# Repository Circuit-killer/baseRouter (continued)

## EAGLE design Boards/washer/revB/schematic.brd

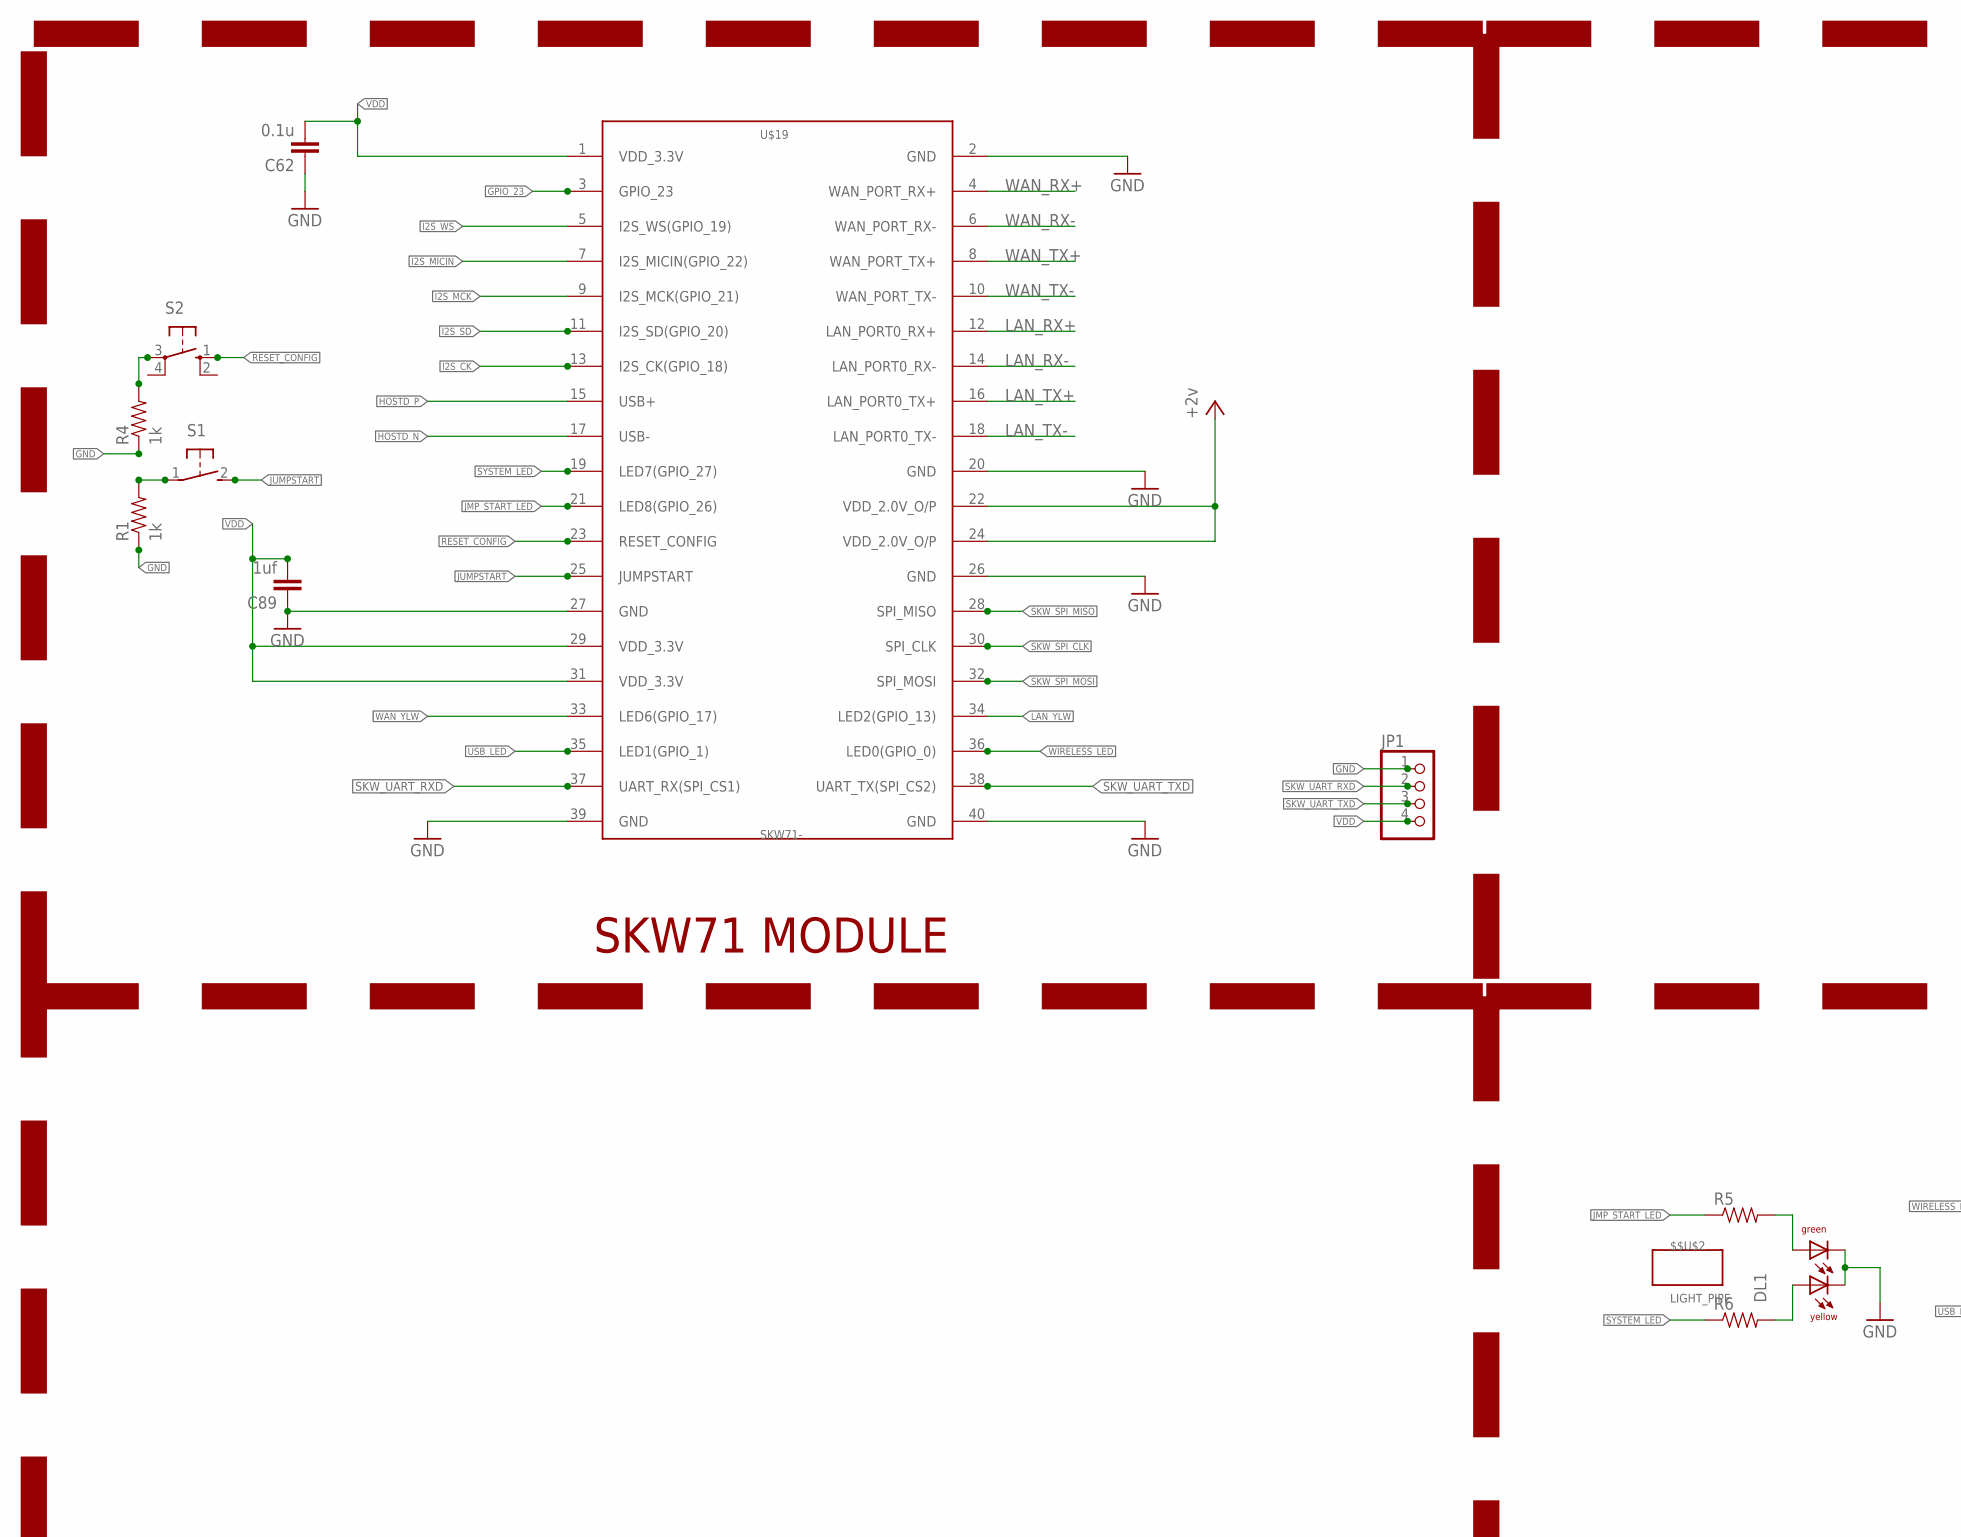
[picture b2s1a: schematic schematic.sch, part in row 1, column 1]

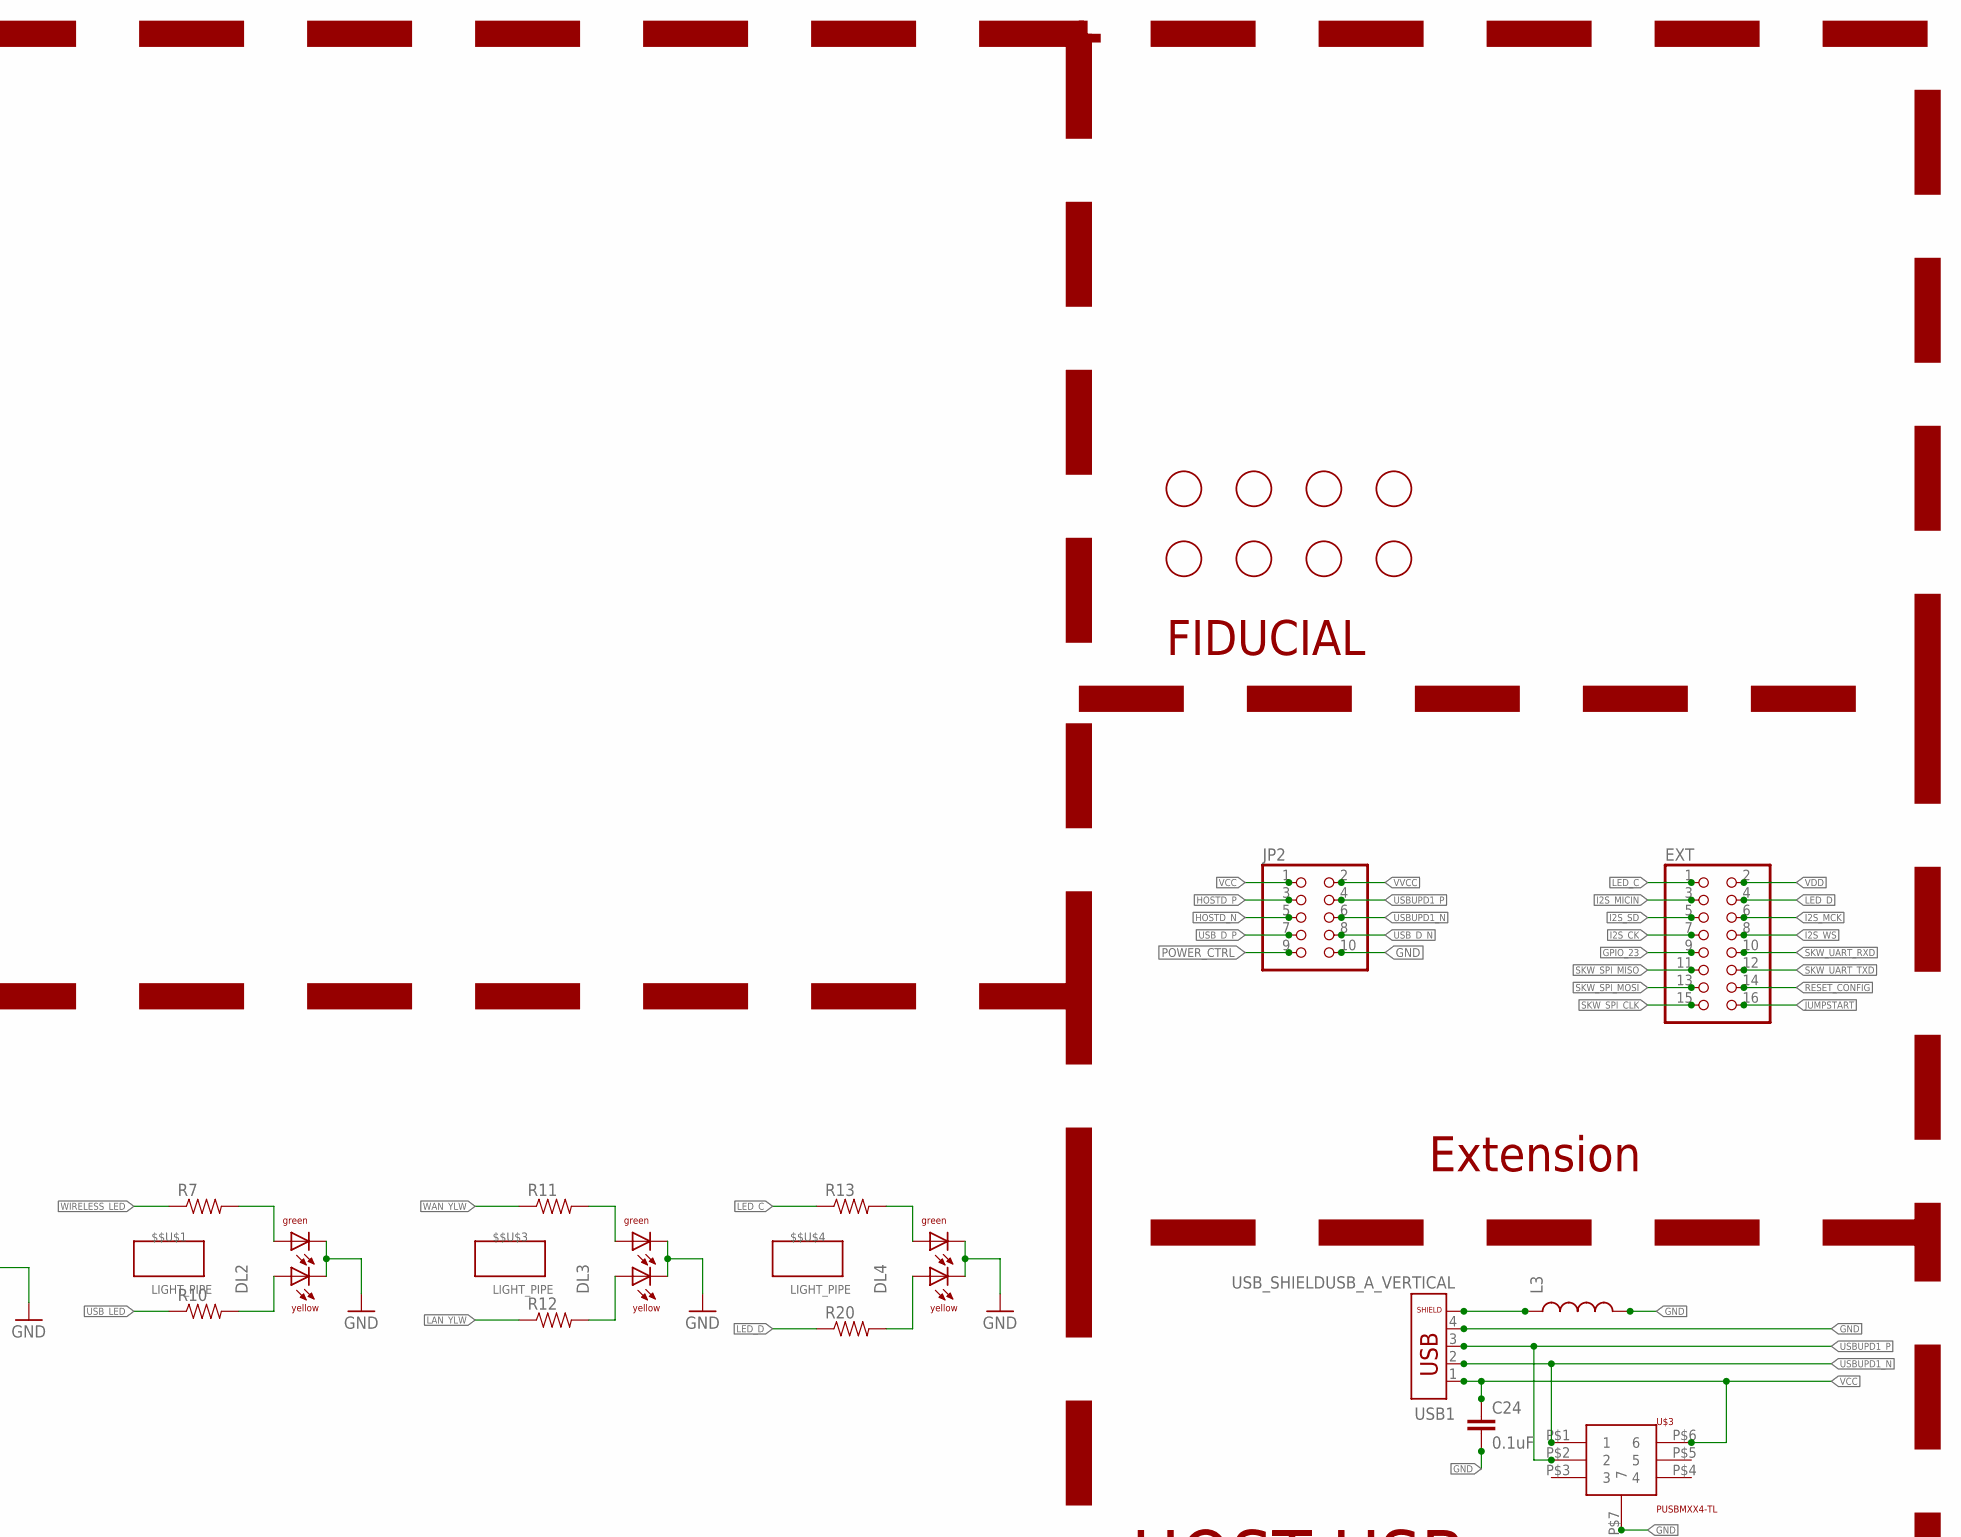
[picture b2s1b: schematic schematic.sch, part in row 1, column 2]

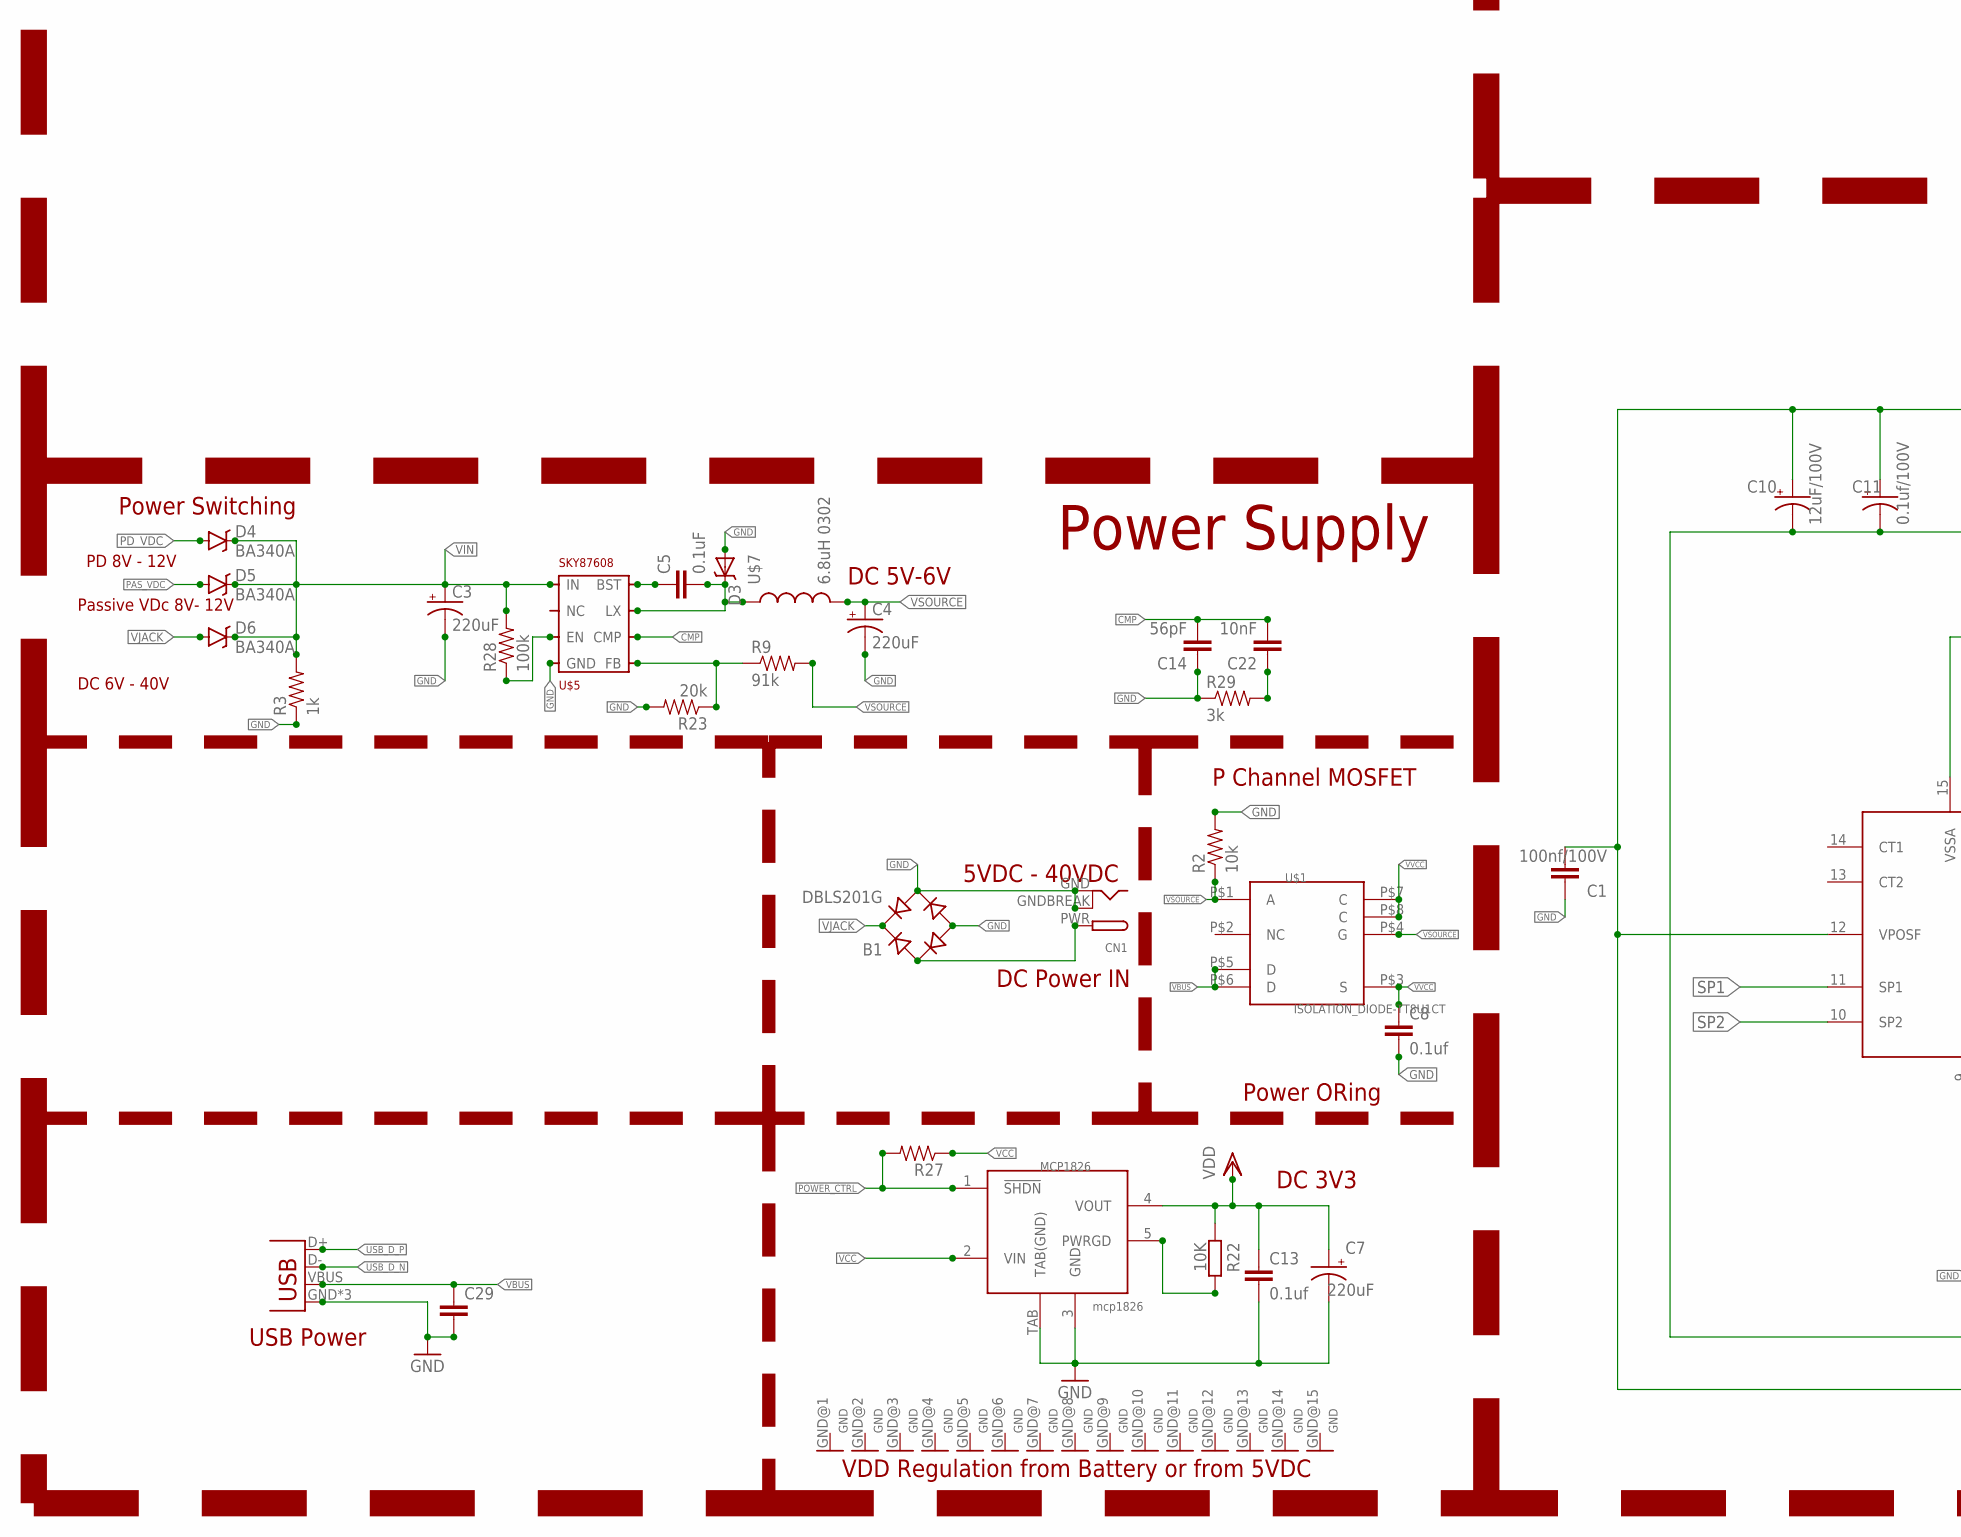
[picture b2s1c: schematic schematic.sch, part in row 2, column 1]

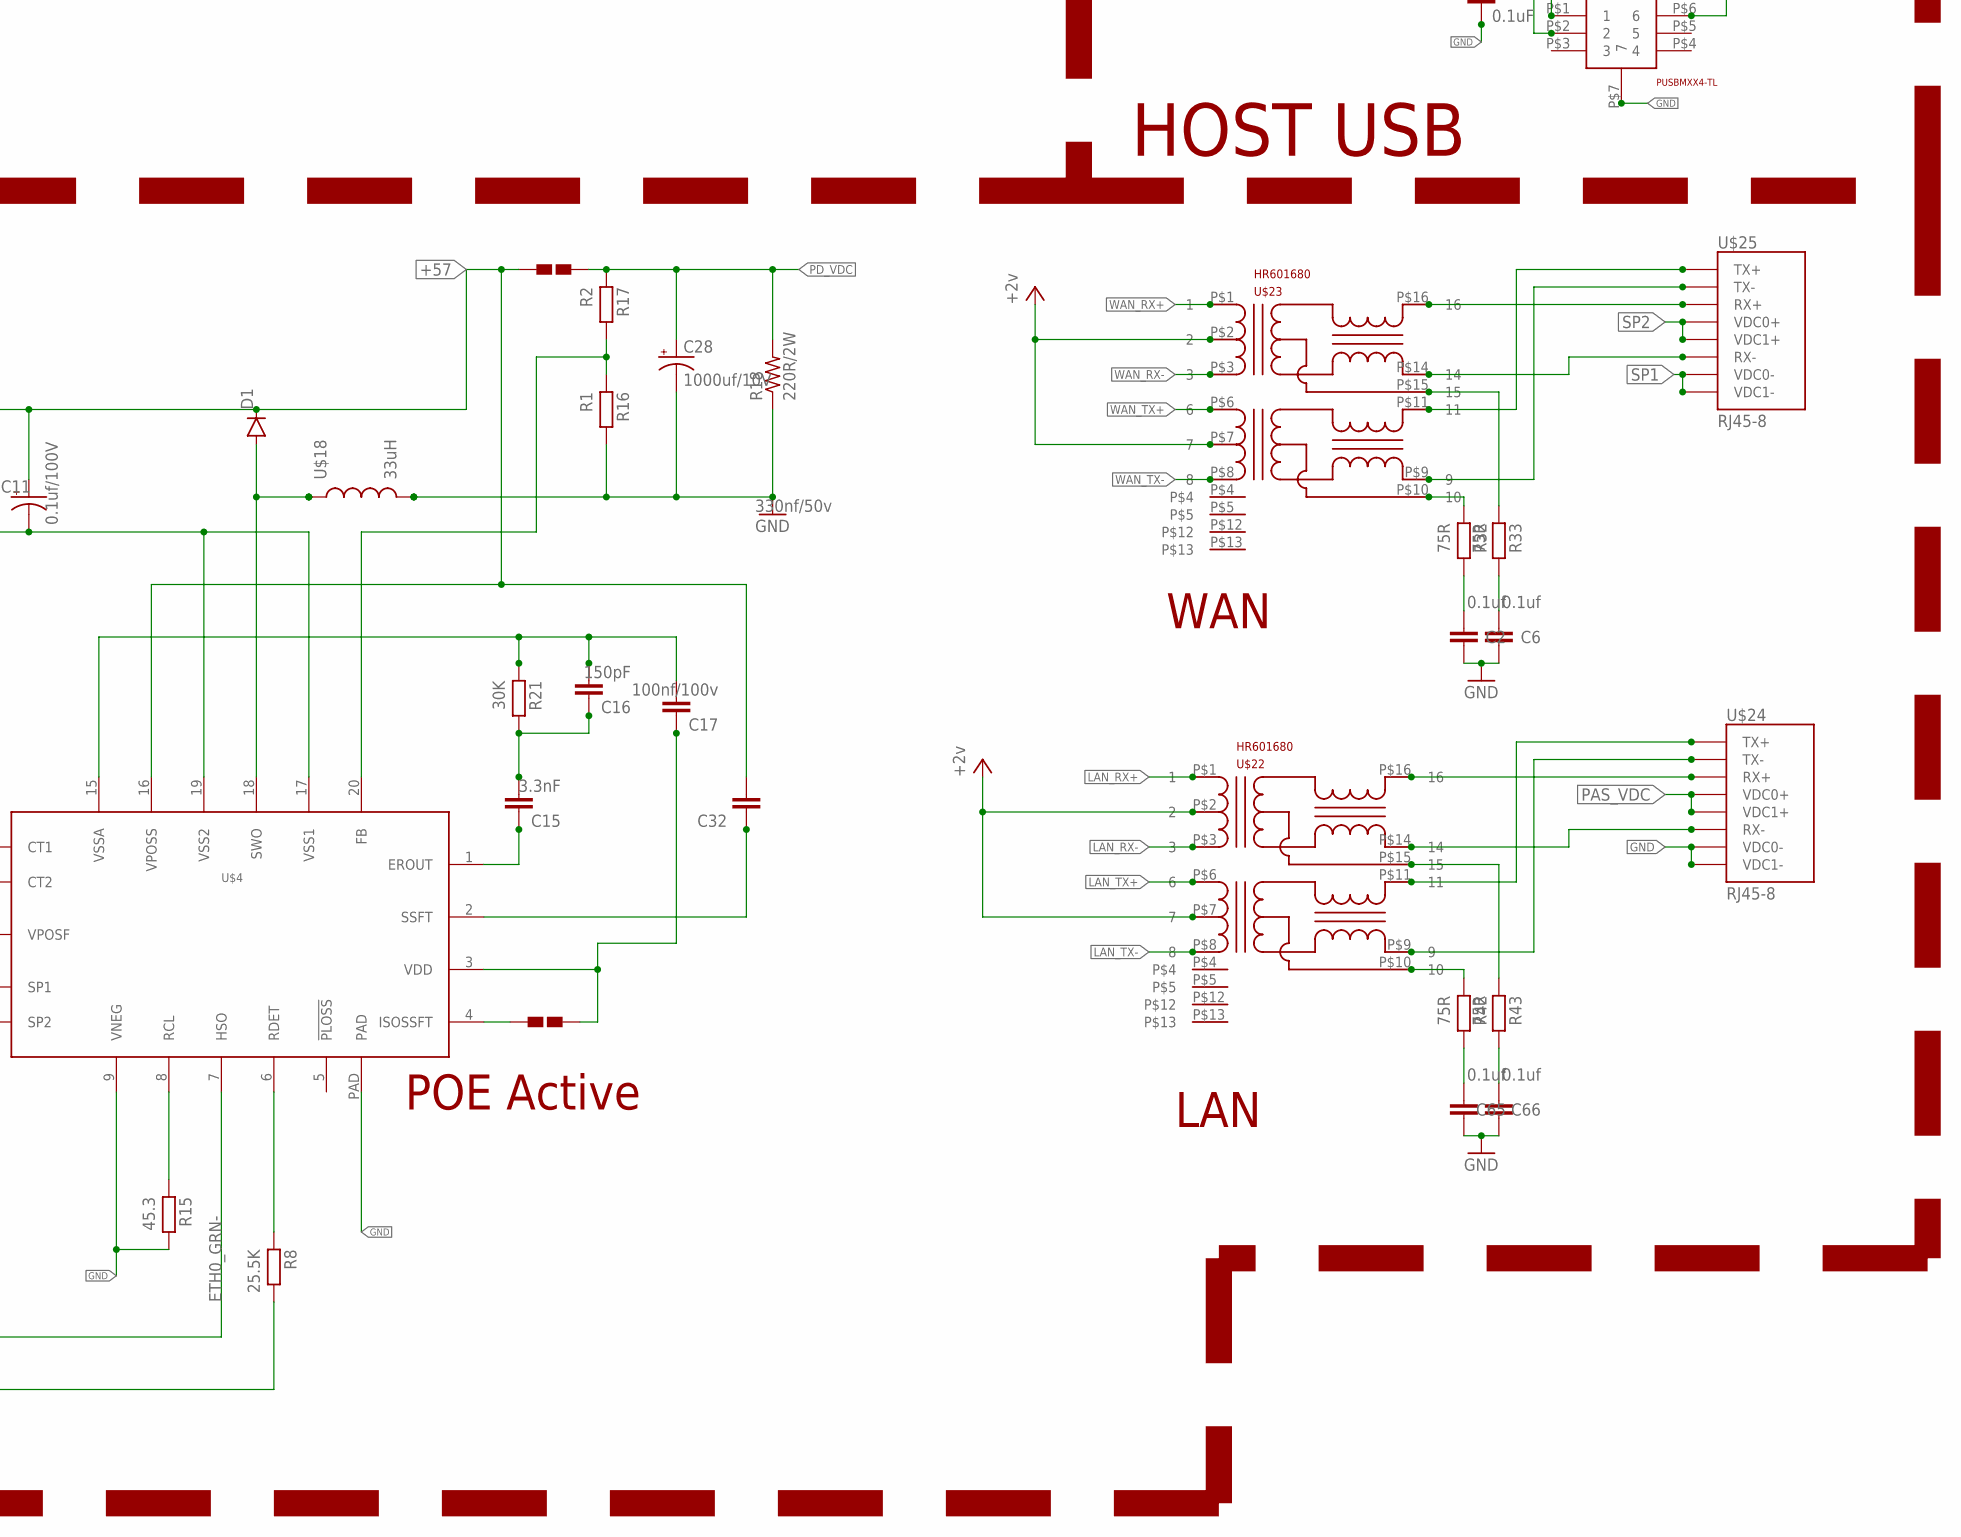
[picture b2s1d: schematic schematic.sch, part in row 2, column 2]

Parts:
$$U$1, $$U$2, $$U$3, $$U$4: LIGHT_PIPE; LIGHT-PIPE
B1: DBLS201G; DBS
C1: 100nf/100V; C0805
C2, C6, C65, C66: 0.1uf; C0603
C3: 220uF; E3,5-10
C4, C7: 220uF; E5-10,5
C5, C24: 0.1uF; 0402-CAP
C8, C13: 0.1uf; C0402
C10: 12uF/100V; E2,5-6E
C11: 0.1uf/100V; E2-5
C14: 56pF; 0402-CAP
C15: 3.3nF; C0805
C16: 150pF; C0805
C17: 100nf/100v; C0805
C22: 10nF; 0402-CAP
C28: 1000uf/10V; E5-13
C29: CAP0402-CAP; 0402-CAP
C32: 330nf/50v; C0805
C62: 0.1u; C0603
C89: 1uf; C0603
CN1: DCBARRELPTH; DCJACK_2MM_PTH
D1: DIODESMC/DO-214AB; SMC
D3: DIODE-SCHOTTKY_; SMA-DIODE
D4, D5, D6: BA340A; SMA-DIODE
DL1, DL2, DL3, DL4: DUOLED-1X2; DUOLED-C-0603
EXT: PINHD-2X8; 2X08
JP1: PINHD-1X4; 1X04
JP2: PINHD-2X5; 2X05
JP4: USB-MICROB
L3: INDUCTOR0402; C0402
MCP1826: mcp1826; SOT223-5
R1, R3, R4: 1k; 0402-RES
R2: 10k; 0402-RES
R5, R6, R7, R10, R11, R12, R13, R20, R27: RESISTOR0402-RES; 0402-RES
R8: 25.5K; R0603
R9: 91k; 0402-RES
R15: 45.3; R0603
R16: R1; R0603
R17: R2; R0603
R18: 220R/2W; R2512
R21: 30K; R0603
R22: 10K; R0402
R23: 20k; 0402-RES
R28: 100k; 0402-RES
R29: 3k; 0402-RES
R32, R33, R42, R43: 75R; R0603
S1: 31-XX; B3F-31XX
S2: 10-XX; B3F-10XX
U$1: ISOLATION_DIODE-TT8U1CT; 8-TSST
U$3: PUSBMXX4-TL
U$4: SI3402
U$5: SKY87608; 8PIN-SOP-8L-EP
U$7: 6.8uH 0302; SRN6045
U$9, U$11, U$12, U$13, U$14, U$15, U$16, U$17: FIDUCIAL; FIDUCIAL_1MM
U$10, U$28: SOL-PAD-OPEN
U$18: 33uH; INDUCTOR-10X9.8X6
U$19: SKW71-; SKW71-SMT
U$22, U$23: HR601680; SOIC-16
U$24, U$25: RJ45-8; RJHSE-5080-ND
USB1: USB_SHIELDUSB_A_VERTICAL; USB_A_VERTICAL_PTH

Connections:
+2V: U$19.22 (VDD_2.0V_O/P), U$19.24 (VDD_2.0V_O/P), U$22.P$2 (2), U$22.P$7 (7), U$23.P$2 (2), U$23.P$7 (7)
+57: C1.2, C10.+, C11.+, C32.2, D1.C, R8.2, U$4.12 (VPOSF), U$4.16 (VPOSS), U$28.P$1 (1)
CMP: C14.2, C22.2, U$5.P$6 (CMP)
ETH0_GRN-: C10.-, C11.-, U$4.7 (HSO), U$4.17 (VSS1), U$4.19 (VSS2)
GND: B1.-, B1.AC2, C1.1, C2.1, C3.-, C4.-, C6.1, C7.-, C8.2, C13.2, C14.1, C24.2, C28.-, C29.2, C62.1, C65.1, C66.1, C89.1, CN1.GND, CN1.GNDBREAK, D3.A, DL1.C1, DL1.C2, DL2.C1, DL2.C2, DL3.C1, DL3.C2, DL4.C1, DL4.C2, JP1.1, JP2.10, JP4.GND, JP4.MT1 (GND), JP4.MT2 (GND), L3.2, MCP1826.3 (GND), MCP1826.GND@1 (GND), MCP1826.GND@2 (GND), MCP1826.GND@3 (GND), MCP1826.GND@4 (GND), MCP1826.GND@5 (GND), MCP1826.GND@6 (GND), MCP1826.GND@7 (GND), MCP1826.GND@8 (GND), MCP1826.GND@9 (GND), MCP1826.GND@10 (GND), MCP1826.GND@11 (GND), MCP1826.GND@12 (GND), MCP1826.GND@13 (GND), MCP1826.GND@14 (GND), MCP1826.GND@15 (GND), MCP1826.TAB (TAB(GND)), R1.1, R2.2, R3.1, R4.1, R15.2, R16.2, R18.1, R23.2, R29.1, U$3.P$7 (7), U$4.9 (VNEG), U$4.PAD, U$5.P$4 (GND), U$18.P$2 (2), U$19.2 (GND), U$19.20 (GND), U$19.26 (GND), U$19.27 (GND), U$19.39 (GND), U$19.40 (GND), U$24.P$7 (VDC0-), U$24.P$8 (VDC1-), USB1.4
GPIO_23: EXT.9, U$19.3 (GPIO_23)
HOSTD_N: JP2.5, U$19.17 (USB-)
HOSTD_P: JP2.3, U$19.15 (USB+)
I2S_CK: EXT.7, U$19.13 (I2S_CK(GPIO_18))
I2S_MCK: EXT.6, U$19.9 (I2S_MCK(GPIO_21))
I2S_MICIN: EXT.3, U$19.7 (I2S_MICIN(GPIO_22))
I2S_SD: EXT.5, U$19.11 (I2S_SD(GPIO_20))
I2S_WS: EXT.8, U$19.5 (I2S_WS(GPIO_19))
JMP_START_LED: R5.1, U$19.21 (LED8(GPIO_26))
JUMPSTART: EXT.16, S1.2 (S), U$19.25 (JUMPSTART)
LAN_RX+: U$19.12 (LAN_PORT0_RX+), U$22.P$1 (1)
LAN_RX-: U$19.14 (LAN_PORT0_RX-), U$22.P$3 (3)
LAN_TX+: U$19.16 (LAN_PORT0_TX+), U$22.P$6 (6)
LAN_TX-: U$19.18 (LAN_PORT0_TX-), U$22.P$8 (8)
LAN_YLW: R12.1, U$19.34 (LED2(GPIO_13))
LED_C: EXT.1, R13.1
LED_D: EXT.4, R20.1
unnamed: DL2.A1, R7.2
unnamed: C5.2, D3.C, U$5.P$2 (LX), U$7.1
unnamed: DL1.A1, R5.2
unnamed: DL2.A2, R10.2
unnamed: R1.2, S1.1
unnamed: C16.2, C17.2, R21.1, U$4.15 (VSSA)
unnamed: C15.2, C16.1, R21.2
unnamed: R8.1, U$4.6 (RDET)
unnamed: R15.1, U$4.8 (RCL)
unnamed: R4.2, S2.3
unnamed: U$4.4 (ISOSSFT), U$10.P$1 (1)
unnamed: C17.1, U$4.3 (VDD), U$10.P$2 (2)
unnamed: C15.1, U$4.1 (EROUT)
unnamed: C32.1, U$4.2 (SSFT)
unnamed: R16.1, R17.2, U$4.20 (FB)
unnamed: DL3.A2, R12.2
unnamed: DL4.A1, R13.2
unnamed: MCP1826.5 (PWRGD), R22.2
unnamed: R28.1, U$5.P$7 (EN)
unnamed: C5.1, U$5.P$8 (BST)
unnamed: R9.1, R23.1, U$5.P$5 (FB)
unnamed: DL4.A2, R20.2
unnamed: DL3.A1, R11.2
unnamed: C22.1, R29.2
unnamed: D1.A, U$4.18 (SWO), U$18.P$1 (1)
unnamed: DL1.A2, R6.2
unnamed: L3.1, USB1.P$3 (5)
unnamed: C2.2, R32.2
unnamed: B1.AC1, CN1.PWR
unnamed: C6.2, R33.2
unnamed: U$23.P$16 (16), U$25.P$3 (RX+)
unnamed: U$23.P$14 (14), U$25.P$6 (RX-)
unnamed: R33.1, U$23.P$15 (15)
unnamed: U$23.P$11 (11), U$25.P$1 (TX+)
unnamed: U$23.P$9 (9), U$25.P$2 (TX-)
unnamed: R32.1, U$23.P$10 (10)
unnamed: R42.1, U$22.P$10 (10)
unnamed: U$22.P$9 (9), U$24.P$2 (TX-)
unnamed: U$22.P$11 (11), U$24.P$1 (TX+)
unnamed: R43.1, U$22.P$15 (15)
unnamed: U$22.P$14 (14), U$24.P$6 (RX-)
unnamed: U$22.P$16 (16), U$24.P$3 (RX+)
unnamed: C65.2, R42.2
unnamed: C66.2, R43.2
PAS_VDC: D5.A, U$24.P$4 (VDC0+), U$24.P$5 (VDC1+)
PD_VDC: C28.+, D4.A, R17.1, R18.2, U$28.P$2 (2)
POWER_CTRL: JP2.9, MCP1826.1 (!SHDN), R27.2
RESET_CONFIG: EXT.14, S2.1 (S), U$19.23 (RESET_CONFIG)
SKW_SPI_CLK: EXT.15, U$19.30 (SPI_CLK)
SKW_SPI_MISO: EXT.11, U$19.28 (SPI_MISO)
SKW_SPI_MOSI: EXT.13, U$19.32 (SPI_MOSI)
SKW_UART_RXD: EXT.10, JP1.2, U$19.37 (UART_RX(SPI_CS1))
SKW_UART_TXD: EXT.12, JP1.3, U$19.38 (UART_TX(SPI_CS2))
SP1: U$4.11 (SP1), U$25.P$7 (VDC0-), U$25.P$8 (VDC1-)
SP2: U$4.10 (SP2), U$25.P$4 (VDC0+), U$25.P$5 (VDC1+)
SYSTEM_LED: R6.1, U$19.19 (LED7(GPIO_27))
USBUPD1_N: JP2.6, U$3.P$1 (1), USB1.2
USBUPD1_P: JP2.4, U$3.P$2 (2), USB1.3
USB_D_N: JP2.8, JP4.D-
USB_D_P: JP2.7, JP4.D+
USB_LED: R10.1, U$19.35 (LED1(GPIO_1))
VBUS: C29.1, JP4.VBUS, U$1.P$5 (D), U$1.P$6 (D)
VCC: C24.1, JP2.1, MCP1826.2 (VIN), R27.1, U$3.P$6 (6), USB1.1
VDD: C7.+, C13.1, C62.2, C89.2, EXT.2, JP1.4, MCP1826.4 (VOUT), R22.1, U$19.1 (VDD_3.3V), U$19.29 (VDD_3.3V), U$19.31 (VDD_3.3V)
VIN: C3.+, D4.C, D5.C, D6.C, R3.2, R28.2, U$5.P$1 (IN)
VJACK: B1.+, D6.A
VSOURCE: C4.+, R2.1, R9.2, U$1.P$1 (A), U$1.P$4 (G), U$7.2
VVCC: C8.1, JP2.2, U$1.P$3 (S), U$1.P$7 (C), U$1.P$8 (C)
WAN_RX+: U$19.4 (WAN_PORT_RX+), U$23.P$1 (1)
WAN_RX-: U$19.6 (WAN_PORT_RX-), U$23.P$3 (3)
WAN_TX+: U$19.8 (WAN_PORT_TX+), U$23.P$6 (6)
WAN_TX-: U$19.10 (WAN_PORT_TX-), U$23.P$8 (8)
WAN_YLW: R11.1, U$19.33 (LED6(GPIO_17))
WIRELESS_LED: R7.1, U$19.36 (LED0(GPIO_0))

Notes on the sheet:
POE Active
SKW71 MODULE
5VDC - 40VDC
PD 8V - 12V
Passive VDc 8V- 12V
Power Switching
USB Power
VDD Regulation from Battery or from 5VDC
DC Power IN
Power Supply
DC 5V-6V
DC 6V - 40V
DC 3V3
Power ORing
P Channel MOSFET
HOST USB
Extension
FIDUCIAL
LAN
WAN

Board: 2 copper layers, 97 parts (6 on the bottom side), 96 nets, no tracks yet.

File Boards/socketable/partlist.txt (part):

Partlist

Exported from schematic.sch at 2/14/2015 1:35:12 PM

EAGLE Version 6.5.0 Copyright (c) 1988-2013 CadSoft

Assembly variant: 

Part     Value                    Device                   Package            Library               Sheet

+2V      TPB2,54                  TPB2,54                  B2,54              testpad               1
B1       DBLS201G                 DBLS201G                 DBS                rectifier             1
C1       0.1uF, 50V               CAPACITOR                C0603              BaseApp               1
C2       470uF, 25V               CPOL-EUE3.5-10           E3,5-10            resistor              1
C3       220uF                    CPOL-USE3.5-10           E3,5-10            schematic             1
C4       220uF                    CPOL-USE5-10.5           E5-10,5            schematic             1
C5       0.1uF                    CAPACITOR                C0603              BaseApp               1
C7       220uF                    CPOL-USE5-10.5           E5-10,5            adafruit              1
C8       0.1uF                    CAPACITOR                C0603              BaseApp               1
C9       0.1uF, 50V               CAPACITOR                C0603              BaseApp               1
C10      0.1uF, 50V               CAPACITOR                C0603              BaseApp               1
C11      0.1uF, 50V               CAPACITOR                C0603              BaseApp               1
C12      1nF,2kV                  CAPACITOR                C0603              BaseApp               1
C13      0.1uF                    CAPACITOR                C0603              BaseApp               1
C14      56pF                     CAPACITOR                C0603              BaseApp               1
C22      10nF                     CAPACITOR                C0603              BaseApp               1
C24      0.1uF                    CAPACITOR                C0603              BaseApp               1
C29      0.1uF                    CAPACITOR                C0603              BaseApp               1
C62      0.1uF                    CAPACITOR                C0603              BaseApp               1
C65      0.1uF                    CAPACITOR                C0603              BaseApp               1
C66      0.1uF                    CAPACITOR                C0603              BaseApp               1
C89      1uF                      CAPACITOR                C0603              BaseApp               1
CN1                               DCBARRELPTH              DCJACK_2MM_PTH     adafruit              1
D3       DIODE-SCHOTTKY_          DIODE-SCHOTTKY_          SMA-DIODE          schematic             1
D4       BA340A                   B340A                    SMA-DIODE          SparkFun-DiscreteSemi 1
D5       BA340A                   B340A                    SMA-DIODE          SparkFun-DiscreteSemi 1
D6       BA340A                   B340A                    SMA-DIODE          SparkFun-DiscreteSemi 1
DL1                               DUOLED-1X2               DUOLED-C-0603      BaseApp               1
DL2                               DUOLED-1X2               DUOLED-C-0603      BaseApp               1
DL3                               DUOLED-1X2               DUOLED-C-0603      BaseApp               1
DL4                               DUOLED-1X2               DUOLED-C-0603      BaseApp               1
GND      TPB2,54                  TPB2,54                  B2,54              testpad               1
JP1                               PINHD-2X8                2X08               pinhead               1
JP2                               PINHD-2X5                2X05               pinhead               1
JP4      USB-MICROB               USB-MICROB               USB-MICROB         SparkFun-Connectors   1
L        6.8uH 0302               INDUCTORBOURNS_SRN6045   SRN6045            SparkFun-Passives     1
L3                                INDUCTOR0603             0603               SparkFun-Passives     1
LAN      RJ45-8                   RJ45-8                   RJHSE-5080-ND      schematic             1
MCP1826  mcp1826                  MCP1825T                 SOT223-5           BaseApp               1
PAS_VDC  TPB2,54                  TPB2,54                  B2,54              testpad               1
PD_VDC   TPB2,54                  TPB2,54                  B2,54              testpad               1
PTCTN    PUSBMXX4-TL              PUSBMXX4-TL              PUSBMXX4-TL        schematic             1
R1       1k                       RESISTOR                 R0603              BaseApp               1
R2       10k                      RESISTOR                 R0603              BaseApp               1
R3       1k                       RESISTOR                 R0603              BaseApp               1
R4       1k                       RESISTOR                 R0603              BaseApp               1
R5                                RESISTOR                 R0603              BaseApp               1
R6                                RESISTOR                 R0603              BaseApp               1
R7                                RESISTOR                 R0603              BaseApp               1
R8       75R                      RESISTOR                 R0603              BaseApp               1
R9       91k                      RESISTOR                 R0603              BaseApp               1
R10                               RESISTOR                 R0603              BaseApp               1
R11                               RESISTOR                 R0603              BaseApp               1
R12                               RESISTOR                 R0603              BaseApp               1
R13                               RESISTOR                 R0603              BaseApp               1
R14      75R                      RESISTOR                 R0603              BaseApp               1
R15      75R                      RESISTOR                 R0603              BaseApp               1
R16      75R                      RESISTOR                 R0603              BaseApp               1
R17      22                       RESISTOR                 R0603              BaseApp               1
R18      22                       RESISTOR                 R0603              BaseApp               1
R20                               RESISTOR                 R0603              BaseApp               1
R22      10K                      RESISTOR                 R0603              BaseApp               1
R23      20k                      RESISTOR                 R0603              BaseApp               1
R27                               RESISTOR                 R0603              BaseApp               1
R28      100k                     RESISTOR                 R0603              BaseApp               1
R29      3k                       RESISTOR                 R0603              BaseApp               1
R42      75R                      RESISTOR                 R0603              BaseApp               1
R43      75R                      RESISTOR                 R0603              BaseApp               1
S2                                10-XX                    B3F-10XX           switch-omron          1
SERIAL                            PINHD-1X4                1X04               pinhead               1
SKW      SKW71-                   SKW71-                   SKW71-SMT          BaseApp               1
SMA      RF-SMA                   RF-SMA                   BU-SMA-H           BaseApp               1
SP1      TPB2,54                  TPB2,54                  B2,54              testpad               1
SP2      TPB2,54                  TPB2,54                  B2,54              testpad               1
TP1      TPB2,54                  TPB2,54                  B2,54              testpad               1
TP2      TPB2,54                  TPB2,54                  B2,54              testpad               1
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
